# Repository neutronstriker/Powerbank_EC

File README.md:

Powerbank_EC
============

Circuit schematic and layout of the Control circuit designed for my Powerbank.
However this circuit can be used as a control circuit for any electronic device that works on a rechargeable battery and has a working 
voltage in between 2.5v to 5v.

The link to the source and binary files for the program to be loaded is https://github.com/neutronstriker/Powerbank_TINY

<br /><span xmlns:dct="http://purl.org/dc/terms/" property="dct:title">Powerbank_EC</span> by <span xmlns:cc="http://creativecommons.org/ns#" property="cc:attributionName">NeutroN StrikeR</span> is licensed under a <a rel="license" href="http://creativecommons.org/licenses/by/4.0/">Creative Commons Attribution 4.0 International License</a>.

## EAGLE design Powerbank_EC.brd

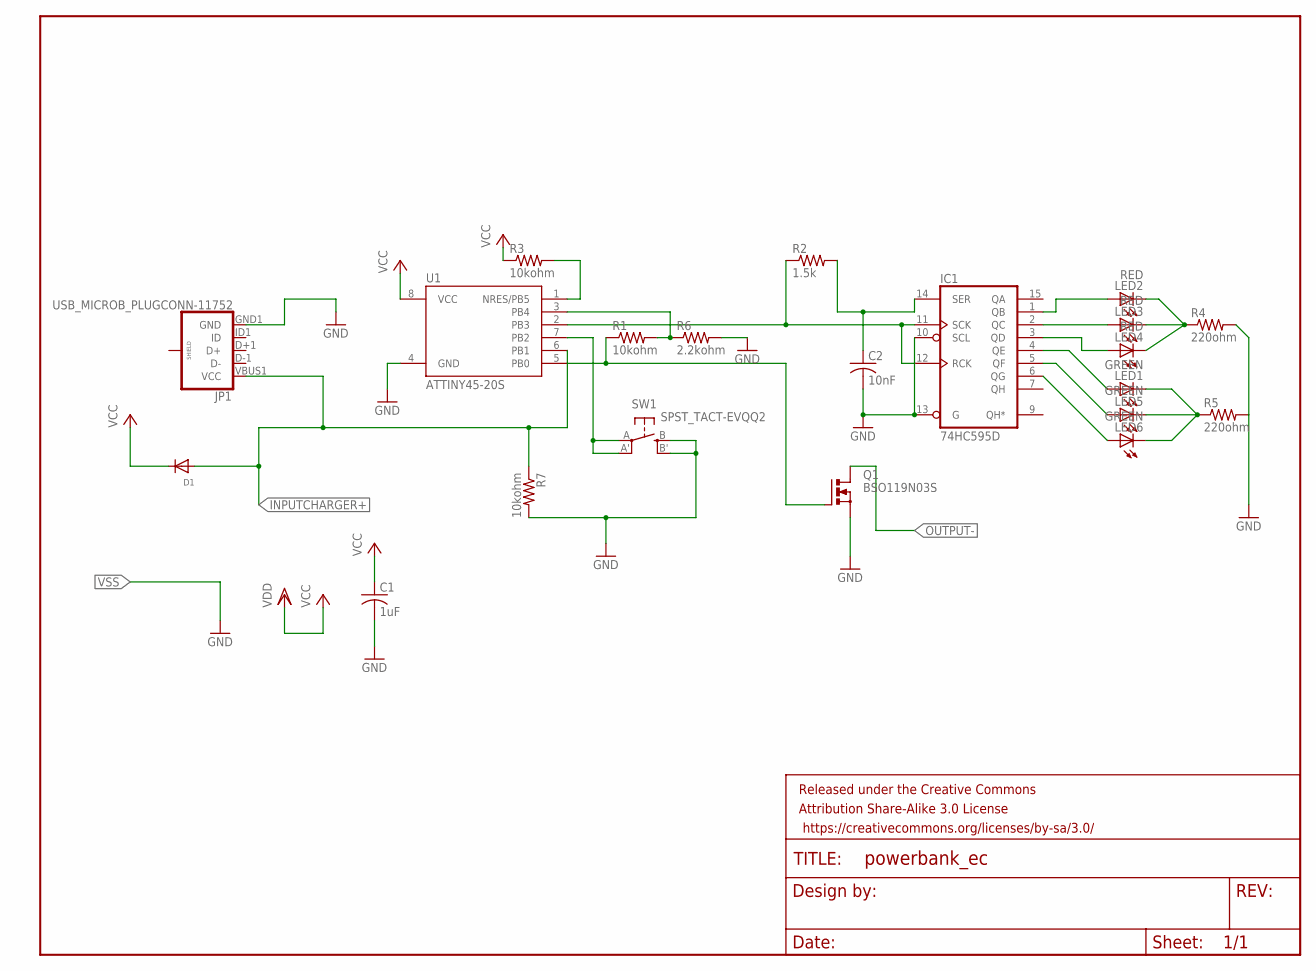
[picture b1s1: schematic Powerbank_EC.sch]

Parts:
C1: 1uF; C1206
C2: 10nF; C1206
D1: DIODESMA; SMADIODE
FRAME1: FRAME-LETTER; CREATIVE_COMMONS
IC1: 74HC595D; SO16
JP1: USB_MICROB_PLUGCONN-11752; USB-B-MICRO-SMD_V03
LED1, LED5, LED6: GREEN; CHIPLED_1206
LED2, LED3, LED4: RED; CHIPLED_1206
Q1: BSO119N03S; SO-08
R1, R3, R7: 10kohm; M1206
R2: 1.5k; M1206
R4, R5: 220ohm; M1206
R6: 2.2kohm; M1206
SW1: SPST_TACT-EVQQ2; EVQ-Q2
U1: ATTINY45-20S; SOIC8_EIAJ_208MIL

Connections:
GND: C1.2, JP1.GND1 (GND), Q1.1 (S), Q1.2 (S), Q1.3 (S), R7.2, SW1.B (S), SW1.B' (S1)
INPUTCHARGER+: D1.A, JP1.VBUS1 (VCC), R7.1, U1.6 (PB1)
unnamed: IC1.1 (QB), LED2.A
unnamed: IC1.2 (QC), LED3.A
unnamed: IC1.3 (QD), LED4.A
unnamed: IC1.4 (QE), LED1.A
unnamed: IC1.5 (QF), LED5.A
unnamed: IC1.6 (QG), LED6.A
unnamed: LED2.C, LED3.C, LED4.C, R4.1
unnamed: LED1.C, LED5.C, LED6.C, R5.1
unnamed: R3.2, U1.1 (NRES/PB5)
unnamed: IC1.11 (SCK), IC1.12 (RCK), R2.1, U1.2 (PB3)
unnamed: SW1.A, SW1.A' (P1), U1.7 (PB2)
unnamed: C2.1, IC1.14 (SER), R2.2
unnamed: R1.2, R6.1, U1.3 (PB4)
unnamed: Q1.4 (G), R1.1, U1.5 (PB0)
OUTPUT-: Q1.5 (D), Q1.6 (D), Q1.7 (D), Q1.8 (D)
VCC: C1.1
VDD: D1.C, IC1.16 (VCC), R3.1, U1.8 (VCC)
VSS: C2.2, IC1.8 (GND), IC1.10 (SCL), IC1.13 (G), R4.2, R5.2, R6.2, U1.4 (GND)

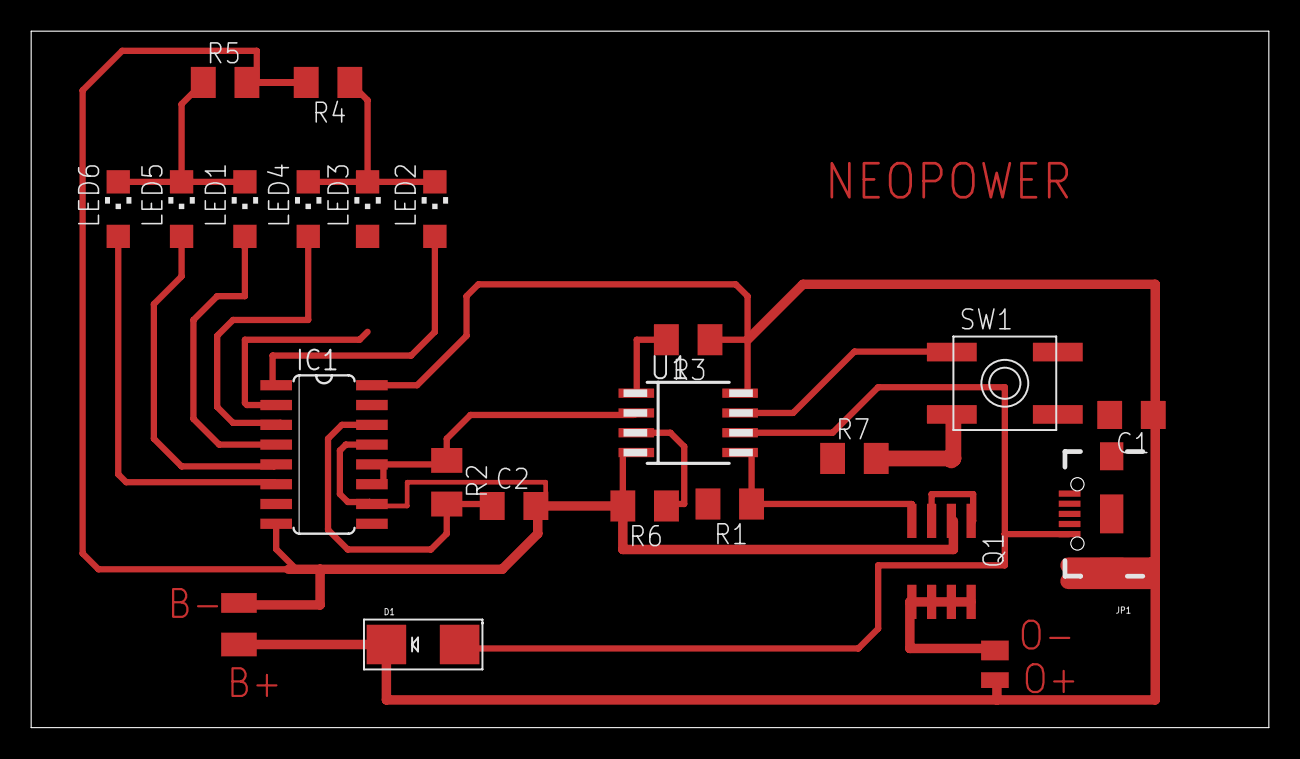
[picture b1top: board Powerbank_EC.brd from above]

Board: 2 copper layers, 79.4 x 44.7 mm, 22 parts (0 on the bottom side), 19 nets.

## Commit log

2015-01-06 :space_invader: Added .gitattributes & .gitignore files
2015-01-06 added files

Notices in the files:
parts and their libraries:
SparkFun-Connectors: Licensing: Creative Commons ShareAlike 4.0 International - https://creativecommons.org/licenses/by-sa/4.0
SparkFun-Retired: Released under the Creative Commons Attribution Share-Alike 3.0 License
SparkFun-Retired: https://creativecommons.org/licenses/by-sa/3.0
